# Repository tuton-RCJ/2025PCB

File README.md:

# 2025PCB
ツートンの基板・回路のリポジトリです。
ご自由にご覧下さい。

基板はすべてKiCAD7.0で設計し、JLCPCB様に発注しています。
1-TOKYOが東東京ノード大会で使用した基板です。
2-KANTOは関東ブロック大会で使用した基板です。
3-NAGOYAは名古屋全国大会で使用した基板です。

# 3-NAGOYA
全国大会機「シロ」の基板です。
全部で6枚です。
## 基板一覧
* 01 MAIN
    メイン基板。一層目に置きます。
* 02 LINE
    ラインセンサ基板。一層目に置きます。
    フォトリフレクタは16個使います。
* 03 FRONT
    正面基板。ToFセンサを搭載しています。
* 04 RESCUE
    二層目と一層目をつなぐ基板です。
* 05 PWR
    電源基板。メイン基板とスペーサで接続します。
* 06 UI
    UI基板。ディスプレイを搭載しています。使いませんでした。
* 07 OpenMV
    OpenMVに取り付けるシールドです。UARTをXHに引き出しました。

# 2-KANTO
関東機体「MIKE（ミケ）」の基板です。
今回は全部で3枚です。

## 基板一覧
* 01 MAIN
    メイン基板。一層目に置きます。
* 02 LINE
    ラインセンサ基板。一層目に置きます。
    フォトリフレクタは16個使います。
* 03 FRONT
    当初は作る予定だったが使わなくなりました。
    空っぽなのもつまらないので回路図に落書きしました。
* 04 PWR
    電源基板。二層目に置きます。

# 1-TOKYO
東東京機体「ポチ」の基板です。
全部で5枚（+α）です。

## 基板一覧
* 01 main
    メイン基板。
    * 完成 2024/10/01
    * 発注 2024/10/02
* 02 top
    ハンドルの上に置く基板。UI基板。
    * 設計中
    * 使わなかった
* 03 front
    正面の基板。カメラとToFを置く。
    * 完成 2024/10/01
    * 発注 2024/10/02
* 04 line
    ラインセンサ基板。
    * 完成 2024/06/25
    * 発注 2024/06/26
* 05 PWR
    電源基板。
    3.3V, 5V, 7.2Vを生成。
    * 完成 2024/06/25
    * 発注 2024/06/26
* 06 WRITER
    書き込み基板
    * 完成 2024/05/14
    * 発注 2024/05/16
* 07 frame
    フレームを基板で作ろうとしたが結局3Dプリンタで作った。
* 08 REG_mod
    TPS5430を使用した自作DCDC。
    電源基板に乗せる。
    * 完成 2024/06/25
    * 発注 2024/06/26
* 09 ToF_mod
    自作ToF（VL53L0X）
    * 完成　2024/08/17
## リポジトリ構成
* 01-main ~ 08-REG_mod 
    それぞれの基板のKiCADのプロジェクト。
* library
    KiCADで使用しているライブラリ。
    シンボル、フットプリント、3Dモデル。
* pin
    STM32のピン配置を考えるために使用したSTM32CubeIDEのファイル。
    かなり雑です。
* ver1、ver2
    過去作の保管場所。
    何らかの事情でボツになった設計たちです。
* PDFファイル
    完成した基板の回路図はPDFにしてあります。
    ブラウザ上で見ることができると思います。

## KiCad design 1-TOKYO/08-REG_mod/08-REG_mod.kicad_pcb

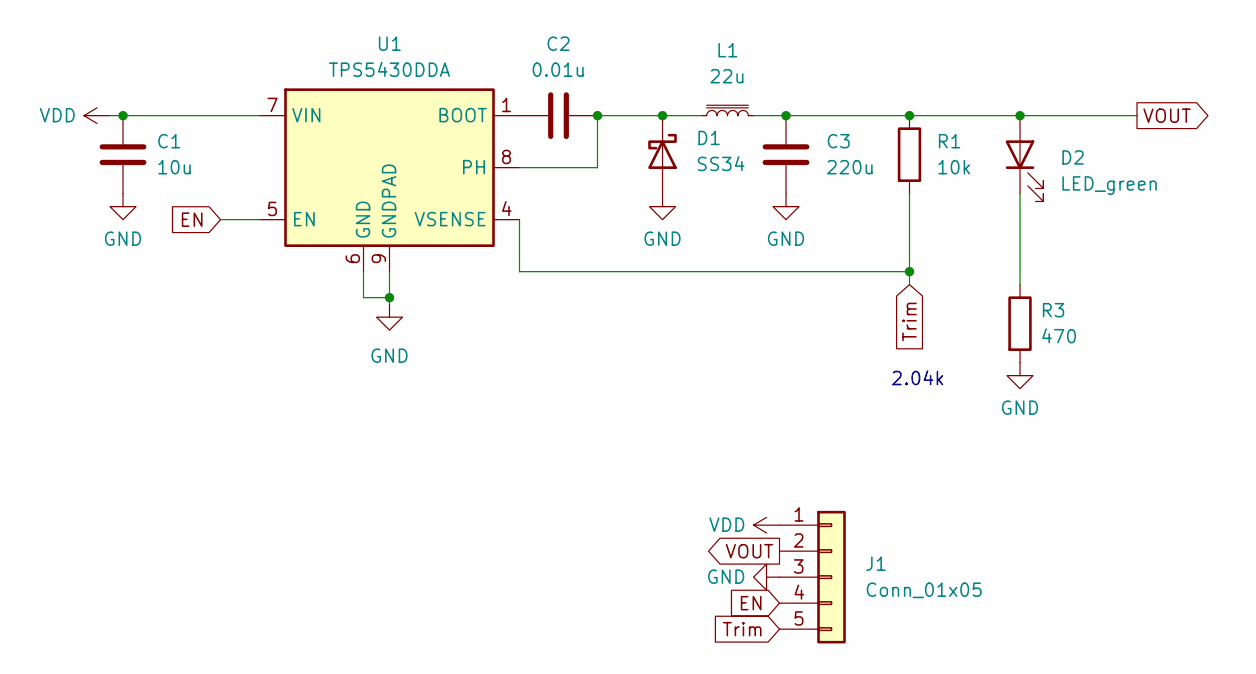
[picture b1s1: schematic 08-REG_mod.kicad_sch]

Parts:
C1: 10u; C_0805_2012Metric; LCSC C15850
C2: 0.01u; C_0603_1608Metric; LCSC C57112
C3: 220u; CP_Radial_D6.3mm_P2.50mm
D1: SS34; D_SMA; LCSC C8678
D2: LED_green; LED_0805_2012Metric; LCSC C2297
J1: Conn_01x05; PinHeader_1x05_P2.54mm_Horizontal
L1: 22u; FXL1040-220-M; LCSC C475917
R1: 10k; R_0603_1608Metric; LCSC C25804
R3: 470; R_0603_1608Metric; LCSC C23179
U1: TPS5430DDA; TI_SO-PowerPAD-8_ThermalVias

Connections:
EN: J1.4, U1.5 (EN)
GND: C1.2, C3.2, D1.2 (A), J1.3, U1.6 (GND), U1.9 (GNDPAD); also elsewhere on the board
unnamed: C2.2, D1.1 (K), L1.1, U1.8 (PH)
unnamed 3: D2.1 (K); also elsewhere on the board
unnamed: C2.1, U1.1 (BOOT)
Trim: J1.5, R1.2, U1.4 (VSENSE)
VDD: C1.1, J1.1, U1.7 (VIN)
VOUT: C3.1, D2.2 (A), J1.2, L1.2, R1.1

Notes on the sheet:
2.04k

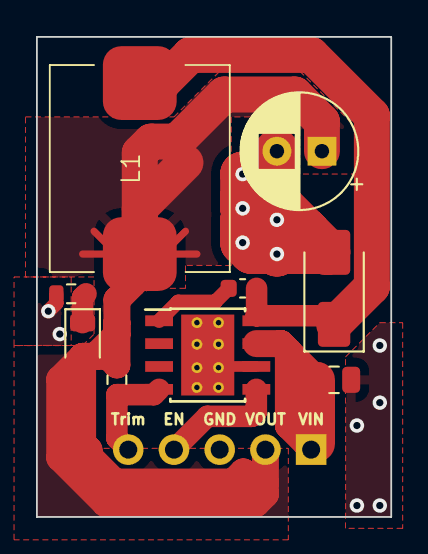
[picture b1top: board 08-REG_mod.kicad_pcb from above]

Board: 2 copper layers, 19.7 x 26.7 mm, 10 parts (1 on the bottom side), 8 nets.

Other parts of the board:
R2: 470; R_0603_1608Metric

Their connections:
GND: R2.2; also elsewhere on the board
unnamed 3: R2.1; also elsewhere on the board

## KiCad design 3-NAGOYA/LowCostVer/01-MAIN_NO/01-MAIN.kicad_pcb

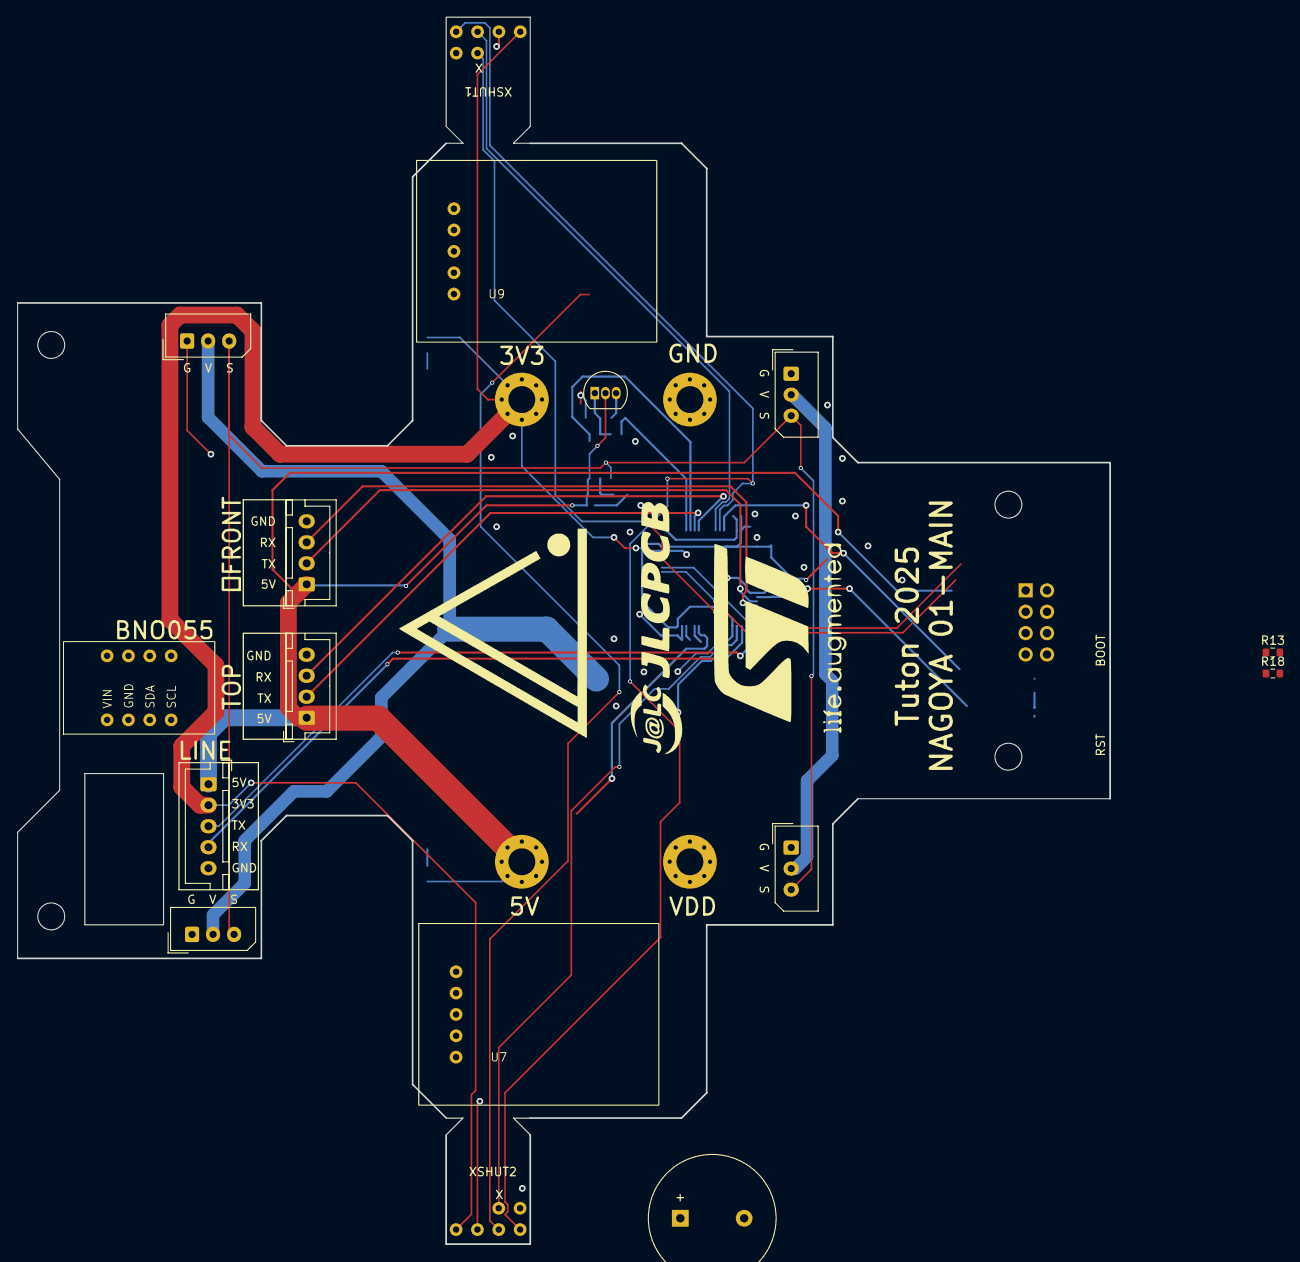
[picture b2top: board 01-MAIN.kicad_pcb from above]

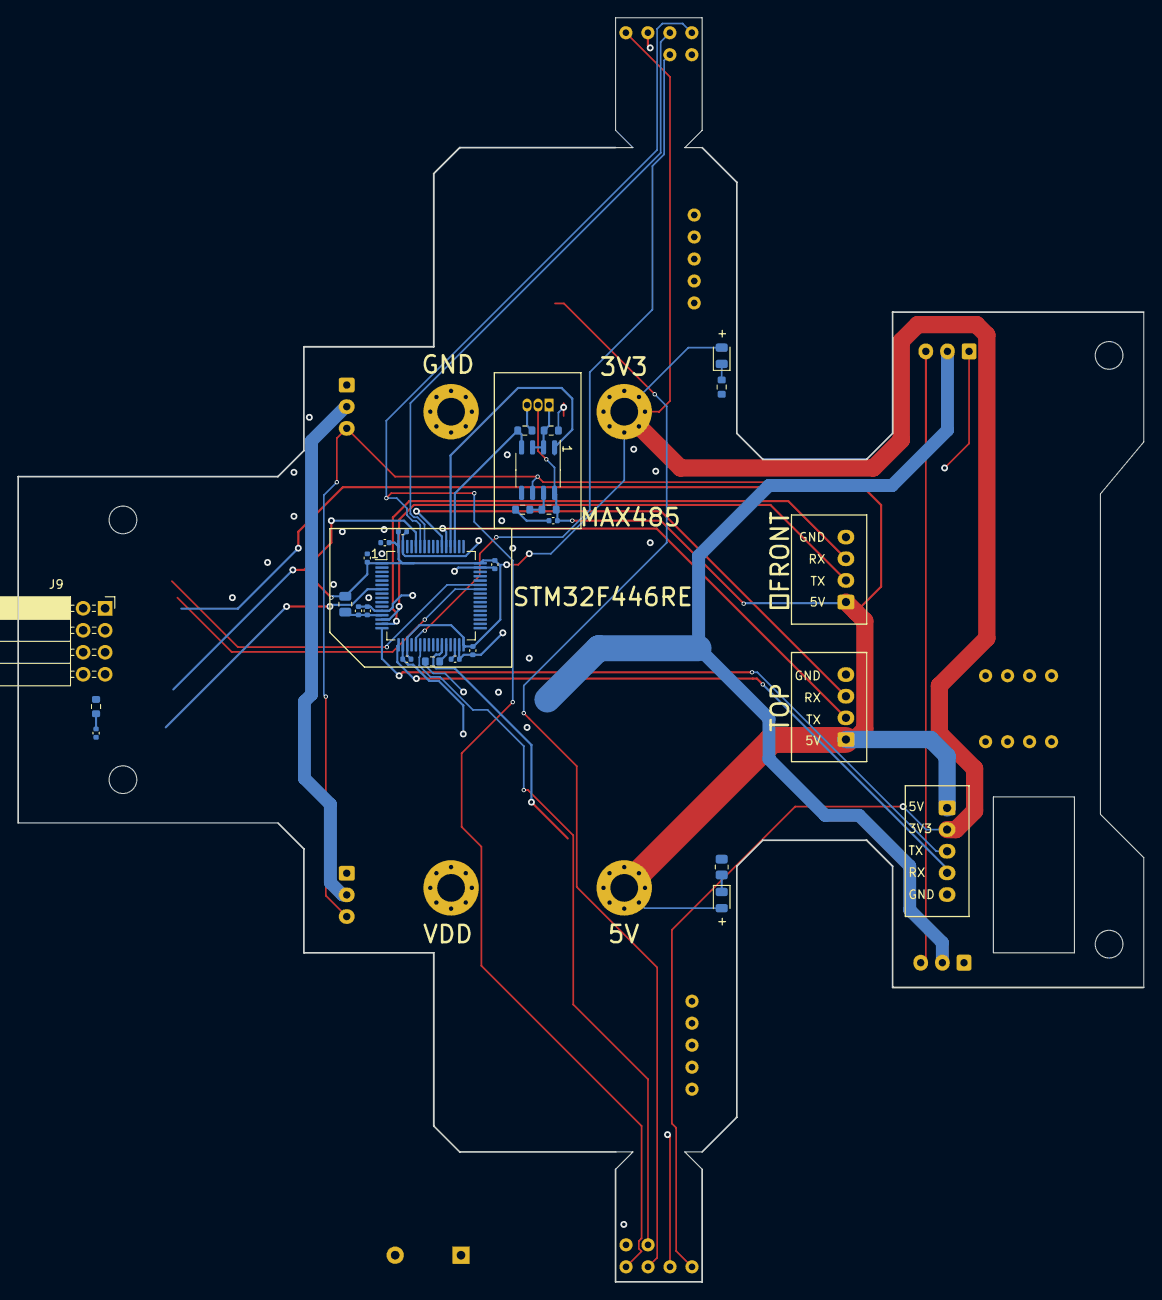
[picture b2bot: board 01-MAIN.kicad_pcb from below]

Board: 2 copper layers, 130.0 x 145.9 mm, 45 parts (25 on the bottom side), 34 nets.

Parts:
BZ1: Buzzer; Buzzer_15x7.5RM7.6
C1, C3, C4, C5, C6, C8, C9, C10: 100n; C_0402_1005Metric
C2, C7: 4.7u; C_0402_1005Metric
C11: 1u; C_0402_1005Metric
D1, D2: LED_GREEN; LED_0805_2012Metric
FB1: FerriteBead; R_0805_2012Metric
H1: ToMainVDD; MountingHole_3.2mm_M3_Pad_Via
H2: ToMainGND; MountingHole_3.2mm_M3_Pad_Via
H3: ToMain3V3; MountingHole_3.2mm_M3_Pad_Via
H4: ToMain5V; MountingHole_3.2mm_M3_Pad_Via
J1: Front; JST_XH_B4B-XH-A_1x04_P2.50mm_Vertical
J2: Top; JST_XH_B4B-XH-A_1x04_P2.50mm_Vertical
J3: toLINE; JST_XH_B5B-XH-A_1x05_P2.50mm_Vertical
J5, J6, J7, J8: STS3032; Molex_SPOX_5267-03A_1x03_P2.50mm_Vertical
J9: WRITER CONN; PinSocket_2x04_P2.54mm_Horizontal
Q1: 2SA1015; TO-92_Inline
R1: 7.5k; R_0603_1608Metric
R2, R6: 10k; R_0603_1608Metric
R3: 20k; R_0603_1608Metric
R4, R5, R13, R18: 2.2k; R_0603_1608Metric
R7: 470; R_0603_1608Metric
R8: 1k; R_0805_2012Metric
U1: STM32F446RETx; LQFP-64_10x10mm_P0.5mm
U2: MAX485ESA; SOP-8_3.9x4.9mm_P1.27mm
U3, U5: vl53l0x_vertical
U4: BNO055
U7, U9: TPS5430_horizontal

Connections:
+3V3: C3.2, C4.2, C5.2, C6.2, C7.1, C8.2, D1.2 (A), FB1.1, H3.1, J3.2, J9.1, U1.1 (VBAT), U1.19 (VDD), U1.32 (VDD), U1.48 (VDD), U1.64 (VDD), U3.1 (3V3), U4.1 (VIN), U5.1 (3V3)
+5V: C9.1, D2.2 (A), H4.1, J1.1, J2.1, J3.1, Q1.2 (C), R4.1, U2.8 (VCC)
BOOT0: J9.4, R2.1, U1.60 (BOOT0)
GND: BZ1.2 (+), C1.1, C2.2, C3.1, C4.1, C5.1, C6.1, C7.2, C8.1, C9.2, C10.1, C11.1, H2.1, J1.4, J2.4, J3.5, J5.1, J6.1, J7.1, J8.1, J9.3, R2.2, R3.2, R5.1, R6.2, R7.1, R8.1, R13.2, R18.2, U1.12 (VSSA), U1.18 (VSS), U1.31 (VSS), U1.47 (VSS), U1.63 (VSS), U2.5 (GND), U3.2 (GND), U4.2 (GND), U5.2 (GND), U7.3 (GND), U9.3 (GND)
I2C1_SCL: U1.58 (PB6), U3.3 (SCL), U4.4 (SCL), U5.3 (SCL)
I2C1_SDA: U1.59 (PB7), U3.4 (SDA), U4.3 (SDA), U5.4 (SDA)
NRST: C1.2, J9.6, U1.7 (NRST)
unnamed: D1.1 (K), R7.2
unnamed: D2.1 (K), R8.2
unnamed: J5.2, J6.2, U7.2 (VOUT)
unnamed: J7.2, J8.2, U9.2 (VOUT)
unnamed: Q1.3 (B), R1.1
unnamed: Q1.1 (E), R3.1, U2.2 (~RE), U2.3 (DE)
unnamed: R6.1, U1.28 (PB2)
unnamed: C2.1, U1.30 (VCAP_1)
unnamed: C10.2, C11.2, FB1.2, U1.13 (VDDA)
unnamed: R4.2, R5.2, U2.7 (B)
unnamed: R13.1, U7.5 (Trim)
unnamed: R18.1, U9.5 (Trim)
STS_SIG: J5.3, J6.3, J7.3, J8.3, U2.6 (A)
UART1_RX: J9.7, U1.43 (PA10)
UART1_TX: J9.5, U1.42 (PA9)
UART2_RX: J3.4, U1.17 (PA3)
UART2_TX: J3.3, U1.16 (PA2)
UART3_RX: U1.52 (PC11), U2.1 (RO)
UART3_TX: R1.2, U1.51 (PC10), U2.4 (DI)
UART4_RX: J1.3, U1.15 (PA1)
UART4_TX: J1.2, U1.14 (PA0)
UART5_RX: J2.3, U1.54 (PD2)
UART5_TX: J2.2, U1.53 (PC12)
VDD: H1.1, U7.1 (VIN), U9.1 (VIN)
XSHUT1: U1.21 (PA5), U3.5 (XSHUT)
XSHUT2: U1.22 (PA6), U5.5 (XSHUT)
buzzer: BZ1.1 (-), U1.27 (PB1)

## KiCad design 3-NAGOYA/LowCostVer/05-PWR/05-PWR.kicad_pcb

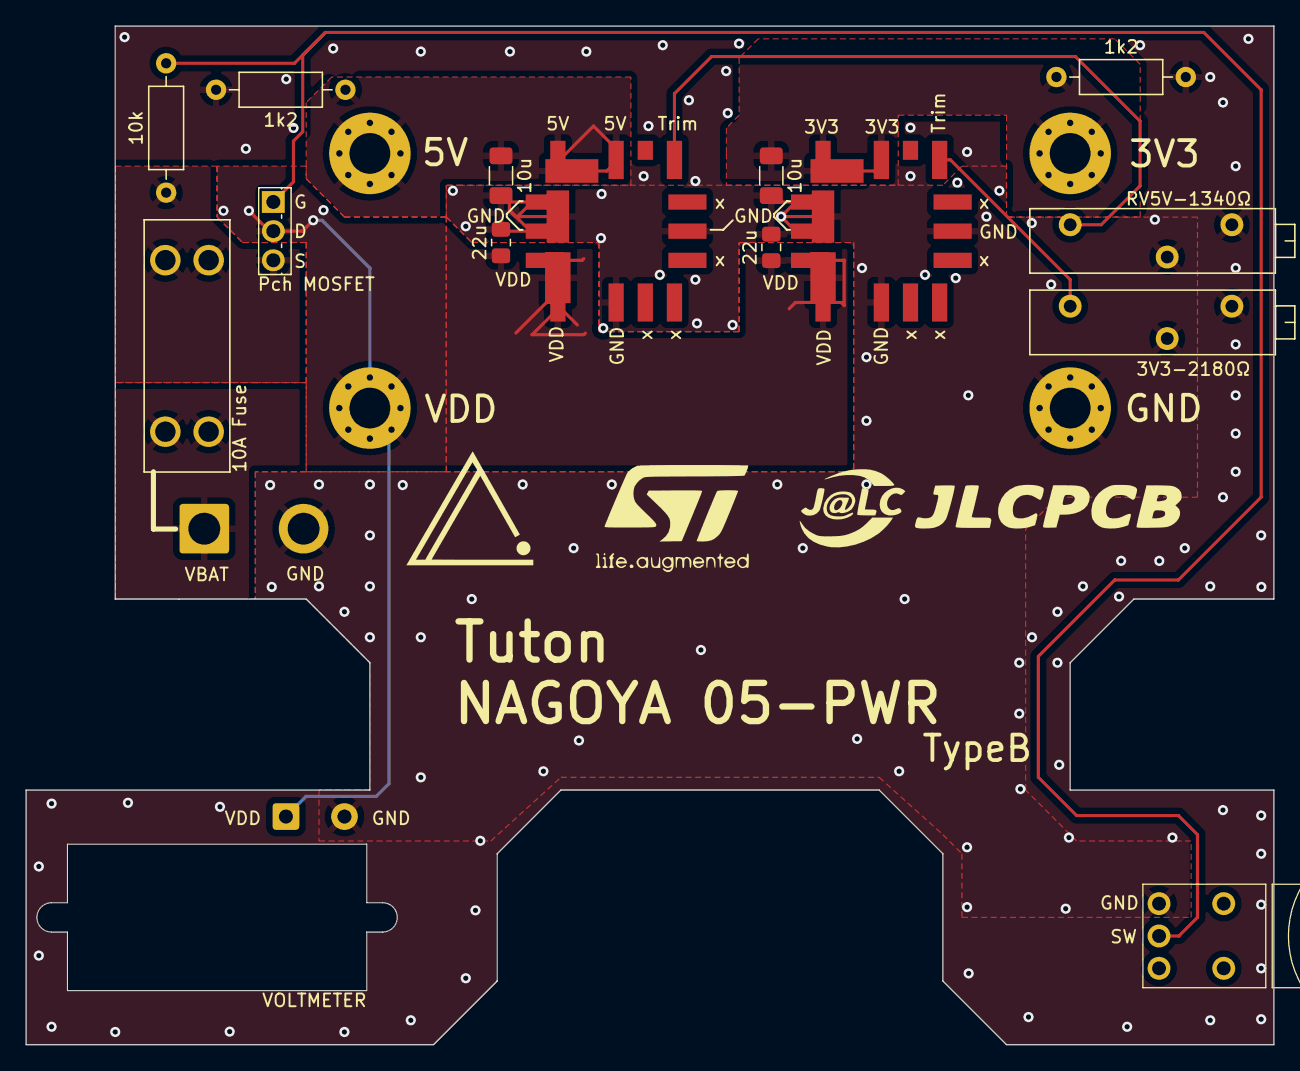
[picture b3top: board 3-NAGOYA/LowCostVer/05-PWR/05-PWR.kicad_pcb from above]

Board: 2 copper layers, 98.0 x 80.0 mm, 20 parts (0 on the bottom side), 9 nets.

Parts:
1k2, 1k2#2: 1.2k; R_Axial_DIN0207_L6.3mm_D2.5mm_P10.16mm_Horizontal
3V3-2180Ω: 3kΩ; Potentiometer_Bourns_3006P_Horizontal
10k: 10k; R_Axial_DIN0207_L6.3mm_D2.5mm_P10.16mm_Horizontal
10u, 10u#2: 10uF; C_1206_3216Metric_Pad1.33x1.80mm_HandSolder
22u, 22u#2: 22uF; C_0805_2012Metric_Pad1.18x1.45mm_HandSolder
F1: Fuse; FUSE_3557-15
H1: ToMainVDD; MountingHole_3.2mm_M3_Pad_Via
H2: ToMainGND; MountingHole_3.2mm_M3_Pad_Via
H3: ToMain3V3; MountingHole_3.2mm_M3_Pad_Via
H4: ToMain5V; MountingHole_3.2mm_M3_Pad_Via
J1: voltmeter; SolderWire-0.5sqmm_1x02_P4.6mm_D0.9mm_OD2.1mm
J2: Battery; SolderWire-2sqmm_1x02_P7.8mm_D2mm_OD3.9mm
Q1: Q_PMOS_GDS; TO-251-3_Vertical
RV5V-1340Ω: 3kΩ; Potentiometer_Bourns_3006P_Horizontal
SW1: SW_SPST; AkizukiSmallRockerSwitchHorizontal
U1, U2: OKL-T6-W12N-C-SMD

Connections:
+3V3: 1k2.1, 10u#2.1, H3.1, U1.4 (Vout), U1.5 (Sense)
+5V: 1k2#2.1, 10u.1, H4.1, U2.4 (Vout), U2.5 (Sense)
GND: 1k2.2, 1k2#2.2, 3V3-2180Ω.2, 3V3-2180Ω.3, 10u.2, 10u#2.2, 22u.2, 22u#2.2, H2.1, J1.2, J2.2, RV5V-1340Ω.2, RV5V-1340Ω.3, SW1.1 (A), U1.1 (ON/OFF), U1.3 (GND), U1.7 (GND), U2.1 (ON/OFF), U2.3 (GND), U2.7 (GND)
unnamed: F1.2, J2.1
unnamed: 10k.2, Q1.1 (G), SW1.2 (B)
unnamed: 10k.1, F1.1, Q1.3 (S)
unnamed: 3V3-2180Ω.1, U1.6 (Trim)
unnamed: RV5V-1340Ω.1, U2.6 (Trim)
VDD: 22u.1, 22u#2.1, H1.1, J1.1, Q1.2 (D), U1.2 (Vin), U2.2 (Vin)

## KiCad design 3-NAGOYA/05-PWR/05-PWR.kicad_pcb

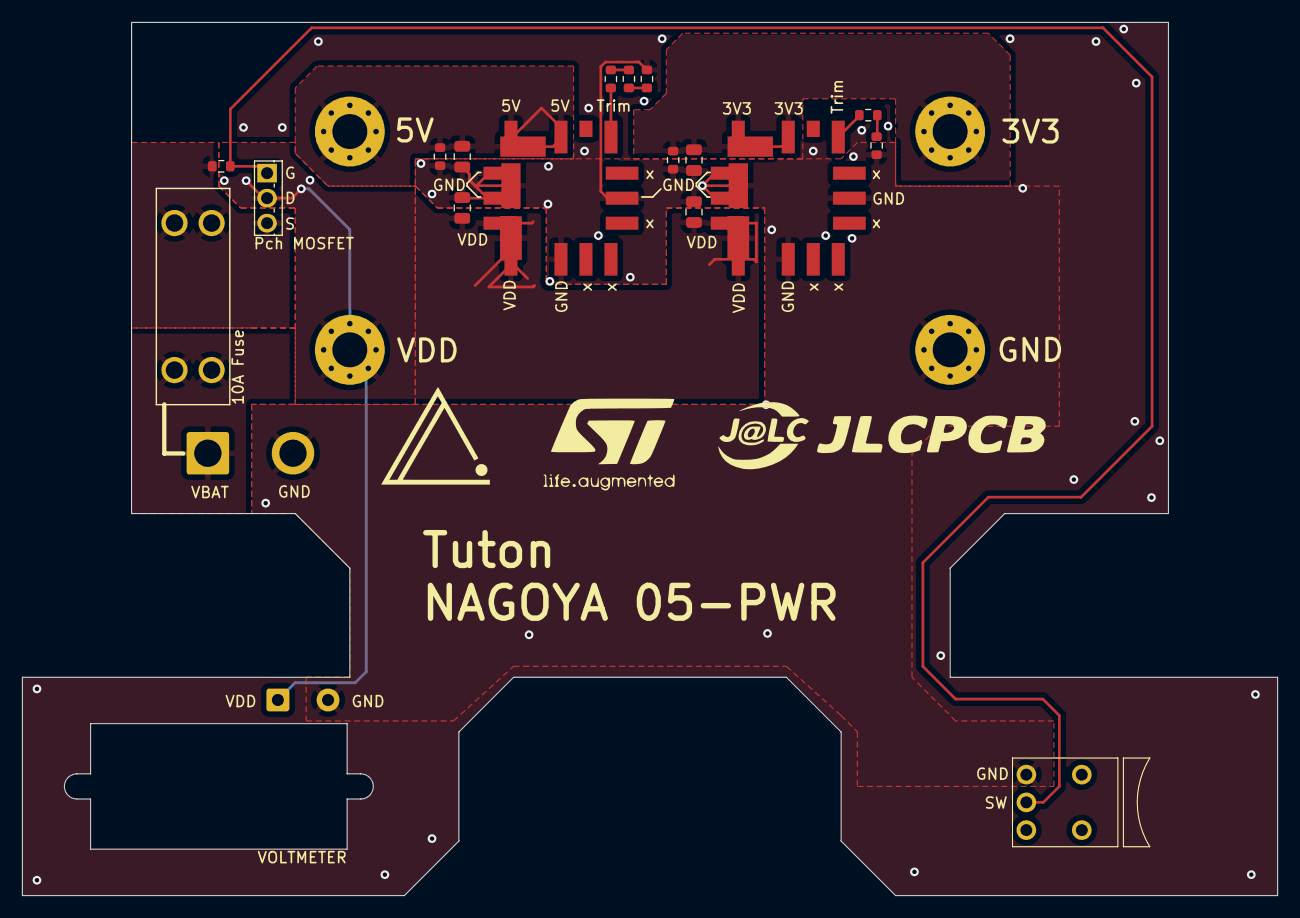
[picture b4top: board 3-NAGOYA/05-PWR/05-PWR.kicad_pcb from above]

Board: 2 copper layers, 115.0 x 80.0 mm, 23 parts (0 on the bottom side), 12 nets.

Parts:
C1, C2: 22uF; C_0805_2012Metric
C3, C4: 10uF; C_0805_2012Metric
F1: Fuse; FUSE_3557-15
H1: ToMainVDD; MountingHole_3.2mm_M3_Pad_Via
H2: ToMainGND; MountingHole_3.2mm_M3_Pad_Via
H3: ToMain3V3; MountingHole_3.2mm_M3_Pad_Via
H4: ToMain5V; MountingHole_3.2mm_M3_Pad_Via
J1: voltmeter; SolderWire-0.5sqmm_1x02_P4.6mm_D0.9mm_OD2.1mm
J2: Battery; SolderWire-2sqmm_1x02_P7.8mm_D2mm_OD3.9mm
Q1: Q_PMOS_GDS; TO-251-3_Vertical
R1: 1k; R_0603_1608Metric
R2: 330; R_0603_1608Metric
R3: 10; R_0603_1608Metric
R4: 1.5k; R_0603_1608Metric
R5: 680; R_0603_1608Metric
R6, R7: 1.2k; R_0603_1608Metric
R8: 10k; R_0603_1608Metric
SW1: SW_SPST; AkizukiSmallRockerSwitchHorizontal
U1, U2: OKL-T6-W12N-C-SMD

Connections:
+3V3: C3.1, H3.1, R6.1, U1.4 (Vout), U1.5 (Sense)
+5V: C4.1, H4.1, R7.1, U2.4 (Vout), U2.5 (Sense)
GND: C1.2, C2.2, C3.2, C4.2, H2.1, J1.2, J2.2, R3.2, R5.2, R6.2, R7.2, SW1.1 (A), U1.1 (ON/OFF), U1.3 (GND), U1.7 (GND), U2.1 (ON/OFF), U2.3 (GND), U2.7 (GND)
unnamed: F1.2, J2.1
unnamed: Q1.1 (G), R8.2, SW1.2 (B)
unnamed: F1.1, Q1.3 (S), R8.1
unnamed: R1.2, R2.1
unnamed: R2.2, R3.1
unnamed: R4.2, R5.1
unnamed: R4.1, U1.6 (Trim)
unnamed: R1.1, U2.6 (Trim)
VDD: C1.1, C2.1, H1.1, J1.1, Q1.2 (D), U1.2 (Vin), U2.2 (Vin)

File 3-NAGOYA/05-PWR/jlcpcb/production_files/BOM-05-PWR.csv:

Comment,Designator,Footprint,LCSC
10uF,"C3,C4",C_0805_2012Metric,C15850
1k,R1,R_0603_1608Metric,C21190
1.2k,"R6,R7",R_0603_1608Metric,C22765
1.5k,R4,R_0603_1608Metric,C22843
10,R3,R_0603_1608Metric,C22859
330,R2,R_0603_1608Metric,C23138
680,R5,R_0603_1608Metric,C23228
10k,R8,R_0603_1608Metric,C25804
22uF,"C1,C2",C_0805_2012Metric,C45783
Fuse,F1,FUSE_3557-15,
~,U2,OKL-T6-W12N-C-SMD,
Q_PMOS_GDS,Q1,TO-251-3_Vertical,
SW_SPST,SW1,AkizukiSmallRockerSwitchHorizontal,
~,U1,OKL-T6-W12N-C-SMD,

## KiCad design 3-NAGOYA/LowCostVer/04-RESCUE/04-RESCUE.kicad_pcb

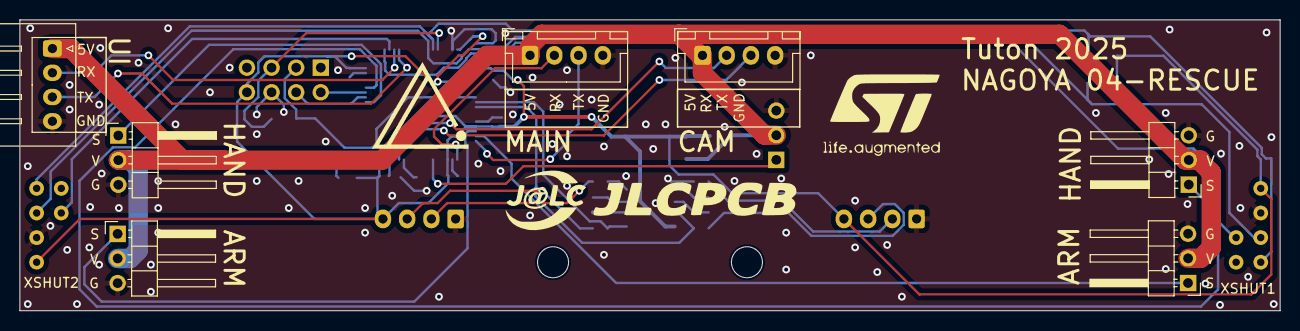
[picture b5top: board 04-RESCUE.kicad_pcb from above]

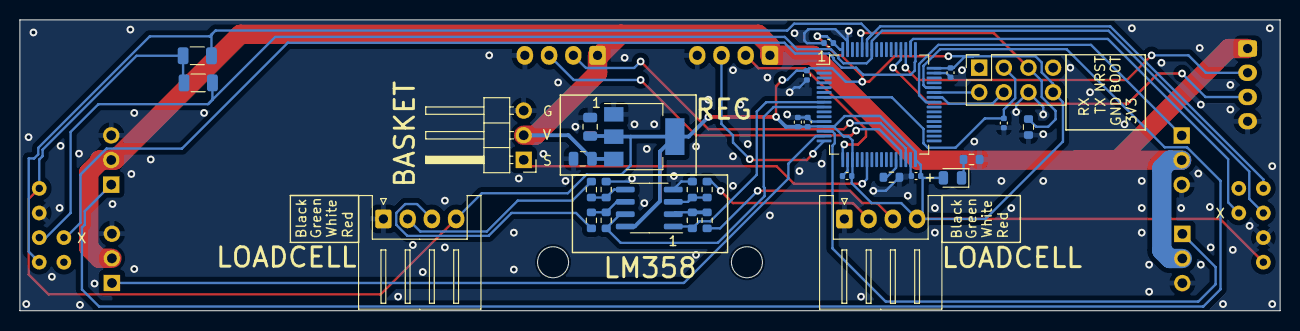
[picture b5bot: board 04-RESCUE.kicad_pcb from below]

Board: 2 copper layers, 130.0 x 30.0 mm, 40 parts (33 on the bottom side), 34 nets.

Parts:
C1, C2: 22u; C_0805_2012Metric
C8, C9, C10, C11, C12, C14, C15: 100n; C_0402_1005Metric
C13: 4.7u; C_0402_1005Metric
D1: LED_GREEN; LED_0805_2012Metric
J1: UI; JST_XH_S4B-XH-A_1x04_P2.50mm_Horizontal
J2: MAIN; JST_XH_B4B-XH-A_1x04_P2.50mm_Vertical
J3: LOADCELL_R; JST_XH_S4B-XH-A_1x04_P2.50mm_Horizontal
J4: WRITER CONN; PinSocket_2x04_P2.54mm_Vertical
J5: LOADCELL_L; JST_XH_S4B-XH-A_1x04_P2.50mm_Horizontal
J6: OpenMV; JST_XH_B4B-XH-A_1x04_P2.50mm_Vertical
M1: ServoBasketLeft; PinHeader_1x03_P2.54mm_Horizontal
M3: ServoArmLeft; PinHeader_1x03_P2.54mm_Horizontal
M4: ServoArmRight; PinHeader_1x03_P2.54mm_Horizontal
M5: ServoHandLeft; PinHeader_1x03_P2.54mm_Horizontal
M6: ServoHandRight; PinHeader_1x03_P2.54mm_Horizontal
R1, R2, R3, R6: 330; R_0603_1608Metric
R4, R5: 10k; R_0603_1608Metric
R7, R8, R9, R10: 1M; R_0603_1608Metric
R11: 470; R_0603_1608Metric
R12, R13: 10k; R_1206_3216Metric
U1: LM358; SOIC-8_3.9x4.9mm_P1.27mm
U2, U3: vl53l0x_vertical
U4: STM32F103RCTx; LQFP-64_10x10mm_P0.5mm
U5: AMS1117-3.3; SOT-223-3_TabPin2

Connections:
+3V3: C2.1, C8.2, C9.2, C10.2, C11.2, C12.2, C13.2, C14.2, D1.2 (A), J3.4, J4.8, J5.4, R12.1, R13.2, U1.8 (V+), U2.1 (3V3), U3.1 (3V3), U4.1 (VBAT), U4.13 (VDDA), U4.19 (VDD), U4.32 (VDD), U4.48 (VDD), U4.64 (VDD), U5.2 (VO)
+5V: C1.1, J1.1, J2.1, J6.1, M1.2 (+), M3.2 (+), M4.2 (+), M5.2 (+), M6.2 (+), U5.3 (VI)
BOOT0: J4.5, R4.1, U4.60 (BOOT0)
GND: C1.2, C2.2, C8.1, C9.1, C10.1, C11.1, C12.1, C13.1, C14.1, C15.1, J1.4, J2.4, J3.1, J4.6, J5.1, J6.4, M1.3 (-), M3.3 (-), M4.3 (-), M5.3 (-), M6.3 (-), R4.2, R5.1, R7.2, R9.2, R11.1, U1.4 (V-), U2.2 (GND), U3.2 (GND), U4.12 (VSSA), U4.18 (VSS), U4.31 (VSS), U4.47 (VSS), U4.63 (VSS), U5.1 (GND)
LOADCEL_L: R10.1, U1.1, U4.8 (PC0)
LOADCEL_R: R8.1, U1.7, U4.9 (PC1)
NRST: C15.2, J4.3, U4.7 (NRST)
unnamed: D1.1 (K), R11.2
unnamed: J3.2, R1.1
unnamed: J3.3, R2.2
unnamed: J5.2, R3.1
unnamed: J5.3, R6.2
unnamed: R3.2, R9.1, U1.3 (+)
unnamed: R6.1, R10.2, U1.2 (-)
unnamed: R1.2, R7.1, U1.5 (+)
unnamed: R2.1, R8.2, U1.6 (-)
unnamed: R5.2, U4.28 (PB2)
SCL: R13.1, U2.3 (SCL), U3.3 (SCL), U4.58 (PB6)
SDA: R12.2, U2.4 (SDA), U3.4 (SDA), U4.59 (PB7)
ServoArmLeft: M3.1 (PWM), U4.14 (PA0)
ServoArmRight: M4.1 (PWM), U4.15 (PA1)
ServoBasket: M1.1 (PWM), U4.22 (PA6)
ServoHandLeft: M5.1 (PWM), U4.41 (PA8)
ServoHandRight: M6.1 (PWM), U4.44 (PA11)
UART1_RX: J4.2, U4.43 (PA10)
UART1_TX: J4.4, U4.42 (PA9)
UART2_RX: J2.2, U4.17 (PA3)
UART2_TX: J2.3, U4.16 (PA2)
UART3_RX: J6.2, U4.30 (PB11)
UART3_TX: J6.3, U4.29 (PB10)
UART4_RX: J1.3, U4.52 (PC11)
UART4_TX: J1.2, U4.51 (PC10)
XSHUT1: U2.5 (XSHUT), U4.49 (PA14)
XSHUT2: U3.5 (XSHUT), U4.50 (PA15)

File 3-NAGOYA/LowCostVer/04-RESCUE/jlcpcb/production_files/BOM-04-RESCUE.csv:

Comment,Designator,Footprint,LCSC
100n,"C10,C11,C12,C14,C15,C8,C9",C_0402_1005Metric,C1525
10k,"R12,R13",R_1206_3216Metric,C17902
1M,"R10,R7,R8,R9",R_0603_1608Metric,C22935
LED_GREEN,D1,LED_0805_2012Metric,C2297
330,"R1,R2,R3,R6",R_0603_1608Metric,C23138
470,R11,R_0603_1608Metric,C23179
4.7u,C13,C_0402_1005Metric,C23733
10k,"R4,R5",R_0603_1608Metric,C25804
22u,"C1,C2",C_0805_2012Metric,C45783
LM358,U1,SOIC-8_3.9x4.9mm_P1.27mm,C5423
AMS1117-3.3,U5,SOT-223-3_TabPin2,C6186
STM32F103RCTx,U4,LQFP-64_10x10mm_P0.5mm,C8323
ServoArmRight,M4,PinHeader_1x03_P2.54mm_Horizontal,
MAIN,J2,JST_XH_B4B-XH-A_1x04_P2.50mm_Vertical,
OpenMV,J6,JST_XH_B4B-XH-A_1x04_P2.50mm_Vertical,
ServoHandLeft,M5,PinHeader_1x03_P2.54mm_Horizontal,
ServoArmLeft,M3,PinHeader_1x03_P2.54mm_Horizontal,
UI,J1,JST_XH_S4B-XH-A_1x04_P2.50mm_Horizontal,
ServoHandRight,M6,PinHeader_1x03_P2.54mm_Horizontal,
LOADCELL_L,J5,JST_XH_S4B-XH-A_1x04_P2.50mm_Horizontal,
~,U2,vl53l0x_vertical,
LOADCELL_R,J3,JST_XH_S4B-XH-A_1x04_P2.50mm_Horizontal,
ServoBasketLeft,M1,PinHeader_1x03_P2.54mm_Horizontal,
~,U3,vl53l0x_vertical,
WRITER CONN,J4,PinSocket_2x04_P2.54mm_Vertical,

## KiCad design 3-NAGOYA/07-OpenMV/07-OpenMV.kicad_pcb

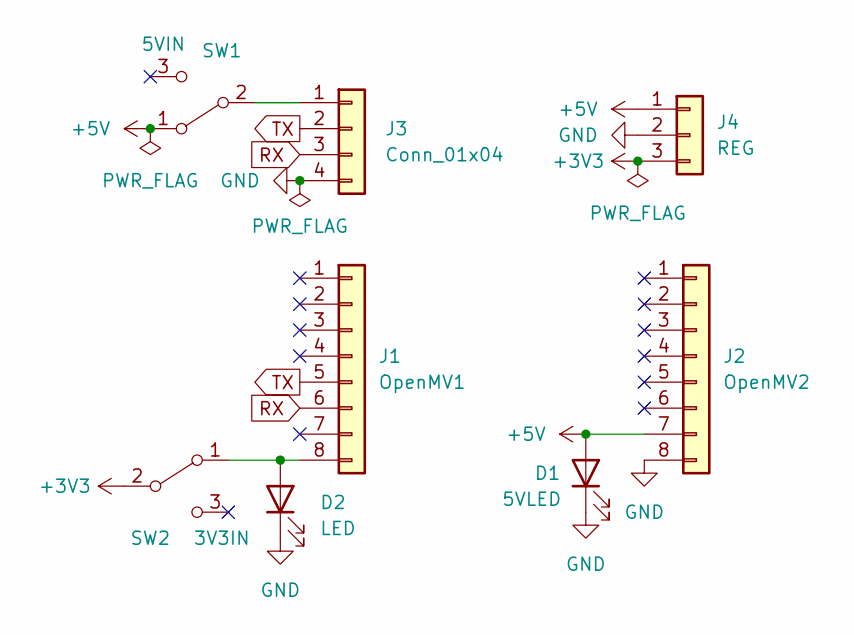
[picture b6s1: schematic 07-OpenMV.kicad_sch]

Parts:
D1: 5VLED; LED_D3.0mm_Clear
D2: LED; LED_D3.0mm_Clear
J1: OpenMV1; PinSocket_1x08_P2.54mm_Vertical
J2: OpenMV2; PinSocket_1x08_P2.54mm_Vertical
J3: Conn_01x04; JST_XH_S4B-XH-A_1x04_P2.50mm_Horizontal
J4: REG; PinHeader_1x03_P2.54mm_Vertical
SW1: 5VIN; SK-12D11VG3
SW2: 3V3IN; SK-12D11VG3

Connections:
+3V3: J4.3, SW2.2 (B)
+5V: D1.2 (A), J2.7, J4.1, SW1.1 (A)
GND: D1.1 (K), D2.1 (K), J2.8, J3.4, J4.2
unnamed: D2.2 (A), J1.8, SW2.1 (A)
unnamed: J3.1, SW1.2 (B)
RX: J1.6, J3.3
TX: J1.5, J3.2

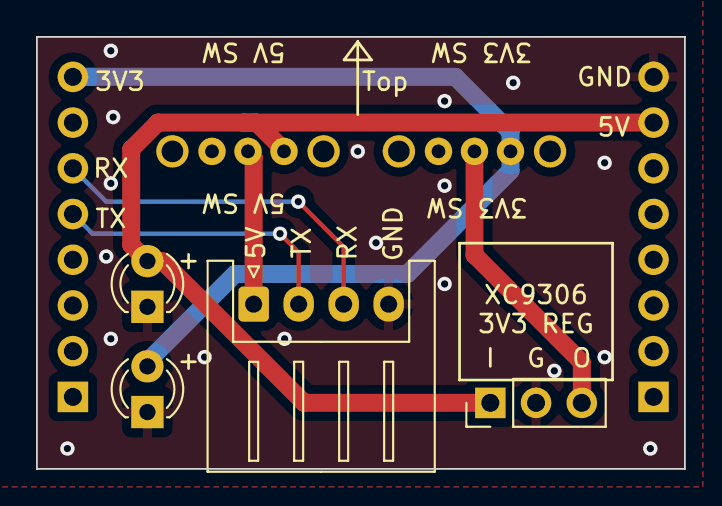
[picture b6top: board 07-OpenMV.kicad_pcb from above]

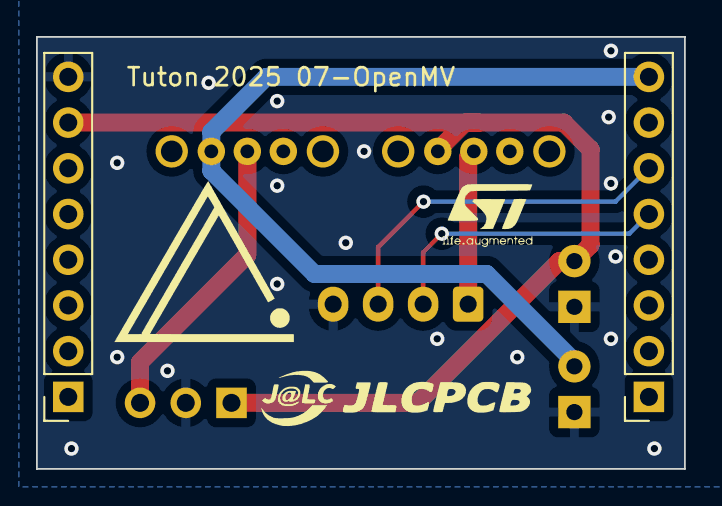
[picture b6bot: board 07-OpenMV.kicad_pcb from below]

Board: 2 copper layers, 36.0 x 24.0 mm, 8 parts (2 on the bottom side), 7 nets.

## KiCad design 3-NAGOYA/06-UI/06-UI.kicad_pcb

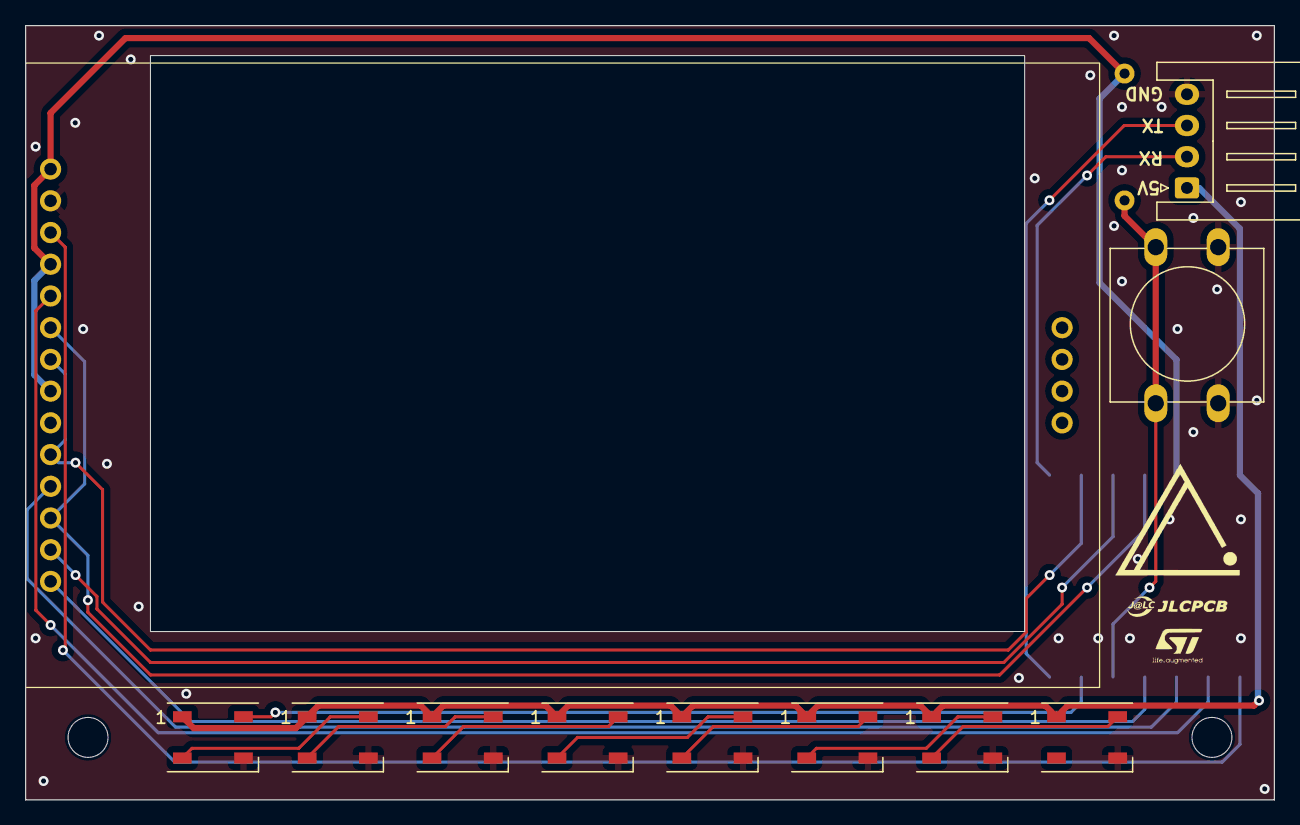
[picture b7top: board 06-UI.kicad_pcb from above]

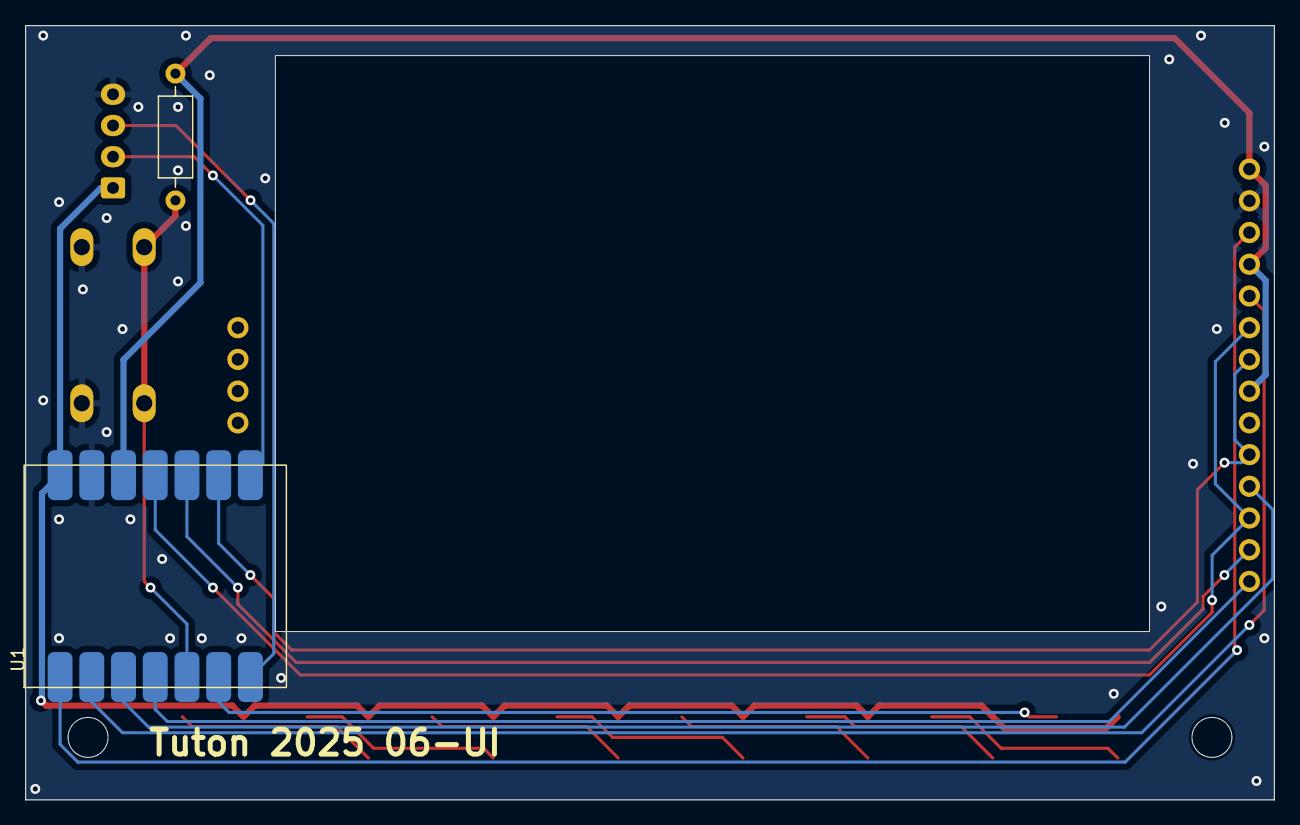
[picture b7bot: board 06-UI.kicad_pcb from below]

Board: 2 copper layers, 100.0 x 62.0 mm, 15 parts (2 on the bottom side), 21 nets.

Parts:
D1, D2, D3, D4, D5, D6, D7, D8: WS2812B; LED_WS2812B_PLCC4_5.0x5.0mm_P3.2mm
H1, H2: MountingHole; MountingHole_3.2mm_M3
J1: OpenMV Conn; JST_XH_S4B-XH-A_1x04_P2.50mm_Horizontal
R1: R; R_Axial_DIN0207_L6.3mm_D2.5mm_P10.16mm_Horizontal
SW1: SW_Push; SW_PUSH-12mm
U1: MOUDLE14P-SMD-2.54-21X17.8MM
U2: MS2807

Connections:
+3V3: R1.2, U1.12 (3V3), U2.1 (VCC), U2.4 (RESET), U2.8 (LED)
+5V: D1.1 (VDD), D2.1 (VDD), D3.1 (VDD), D4.1 (VDD), D5.1 (VDD), D6.1 (VDD), D7.1 (VDD), D8.1 (VDD), J1.1, U1.14 (5V)
Display_CS: U1.1 (D0/A0), U2.3 (CS)
Display_DC: U1.2 (D1/A1), U2.5 (DC/RS)
GND: D1.3 (VSS), D2.3 (VSS), D3.3 (VSS), D4.3 (VSS), D5.3 (VSS), D6.3 (VSS), D7.3 (VSS), D8.3 (VSS), J1.4, SW1.2, U1.13 (GND), U2.2 (GND)
MISO: U1.10 (D9), U2.13 (T_DOUT)
MOSI: U1.11 (D10), U2.6 (MOSI), U2.12 (T_DIN)
unnamed: D1.2 (DOUT), D2.4 (DIN)
unnamed: D2.2 (DOUT), D3.4 (DIN)
unnamed: D3.2 (DOUT), D4.4 (DIN)
unnamed: D4.2 (DOUT), D5.4 (DIN)
unnamed: D5.2 (DOUT), D6.4 (DIN)
unnamed: D6.2 (DOUT), D7.4 (DIN)
unnamed: D7.2 (DOUT), D8.4 (DIN)
RX: J1.2, U1.8 (RX/D7)
SCK: U1.9 (D8), U2.7 (SCK), U2.10 (T_CLK)
SW: R1.1, SW1.1, U1.5 (D4/SDA)
TX: J1.3, U1.7 (D6/TX)
Touch_CS: U1.3 (D2/A2), U2.11 (T_CS)
Touch_IRQ: U1.4 (D3/A3), U2.14 (T_IRQ)
WS2812B: D1.4 (DIN), U1.6 (D5/SCL)

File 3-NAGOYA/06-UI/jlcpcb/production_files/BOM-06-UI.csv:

Comment,Designator,Footprint,LCSC
OpenMV Conn,J1,JST_XH_S4B-XH-A_1x04_P2.50mm_Horizontal,
~,U1,MOUDLE14P-SMD-2.54-21X17.8MM,
~,U2,MS2807,
SW_Push,SW1,SW_PUSH-12mm,
R,R1,R_Axial_DIN0207_L6.3mm_D2.5mm_P10.16mm_Horizontal,
MountingHole,H2,MountingHole_3.2mm_M3,
MountingHole,H1,MountingHole_3.2mm_M3,
WS2812B,D8,LED_WS2812B_PLCC4_5.0x5.0mm_P3.2mm,
WS2812B,D7,LED_WS2812B_PLCC4_5.0x5.0mm_P3.2mm,
WS2812B,D6,LED_WS2812B_PLCC4_5.0x5.0mm_P3.2mm,
WS2812B,D5,LED_WS2812B_PLCC4_5.0x5.0mm_P3.2mm,
WS2812B,D4,LED_WS2812B_PLCC4_5.0x5.0mm_P3.2mm,
WS2812B,D3,LED_WS2812B_PLCC4_5.0x5.0mm_P3.2mm,
WS2812B,D2,LED_WS2812B_PLCC4_5.0x5.0mm_P3.2mm,
WS2812B,D1,LED_WS2812B_PLCC4_5.0x5.0mm_P3.2mm,

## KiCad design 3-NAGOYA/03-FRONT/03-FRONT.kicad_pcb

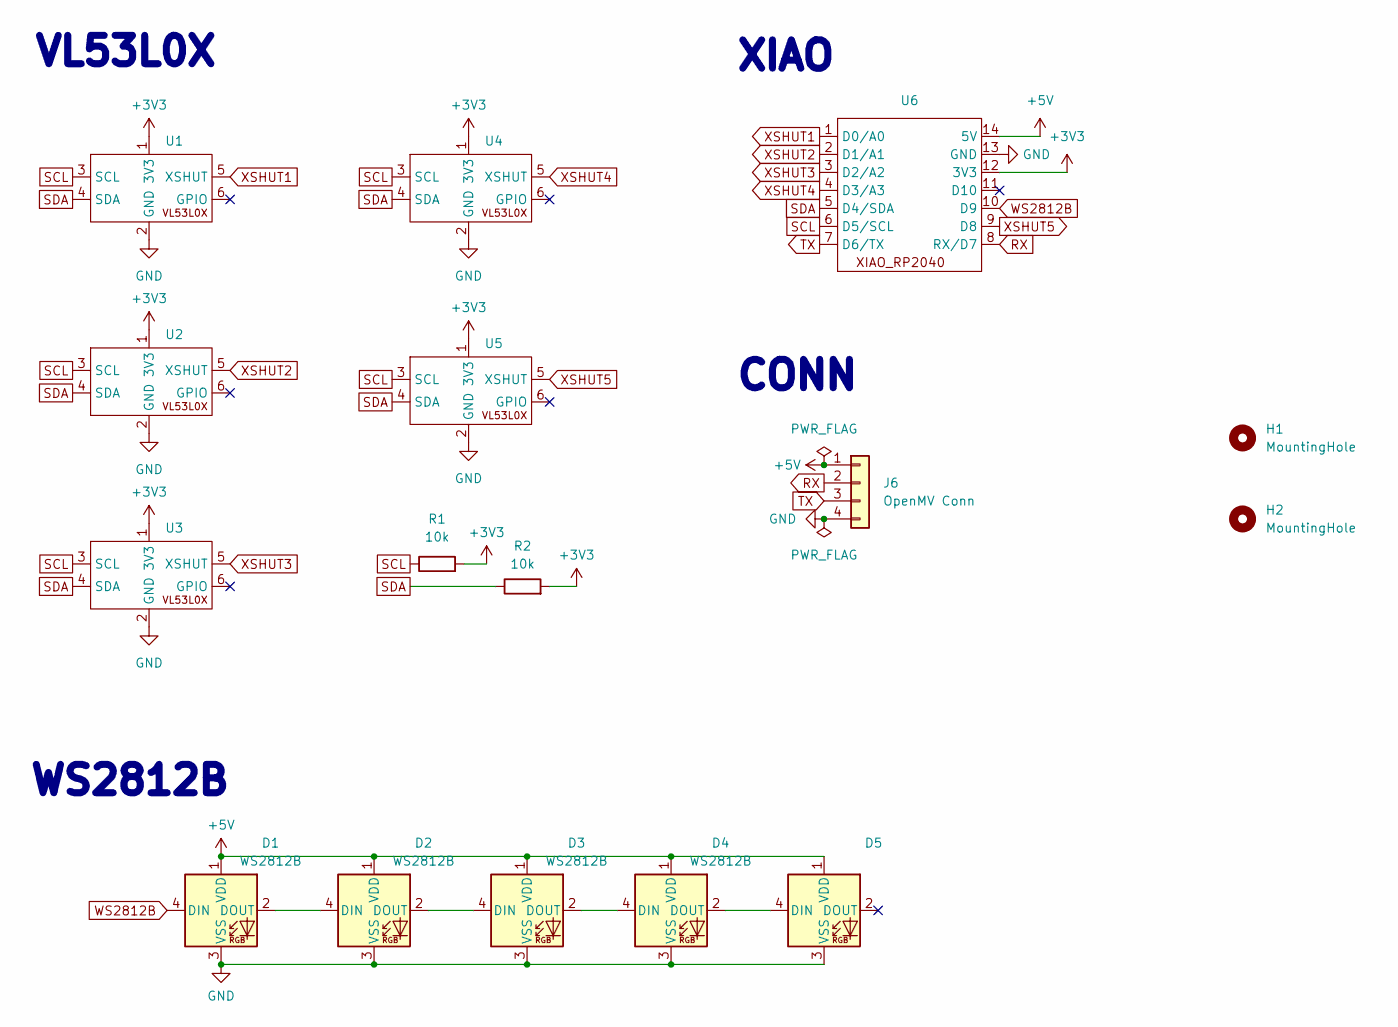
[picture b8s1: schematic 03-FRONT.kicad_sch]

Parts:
D1, D2, D3, D4, D5: WS2812B; LED_WS2812B_PLCC4_5.0x5.0mm_P3.2mm
H1, H2: MountingHole; MountingHole_3.2mm_M3
J6: OpenMV Conn; JST_XH_B4B-XH-A_1x04_P2.50mm_Vertical
R1, R2: 10k; R_Axial_DIN0207_L6.3mm_D2.5mm_P10.16mm_Horizontal
U1, U2, U3, U4, U5: VL53L0X_horizontal
U6: MOUDLE14P-2.54-21X17.8MM

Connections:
+3V3: R1.2, R2.2, U1.1 (3V3), U2.1 (3V3), U3.1 (3V3), U4.1 (3V3), U5.1 (3V3), U6.12 (3V3)
+5V: D1.1 (VDD), D2.1 (VDD), D3.1 (VDD), D4.1 (VDD), D5.1 (VDD), U6.14 (5V); also elsewhere on the board
GND: D1.3 (VSS), D2.3 (VSS), D3.3 (VSS), D4.3 (VSS), D5.3 (VSS), U1.2 (GND), U2.2 (GND), U3.2 (GND), U4.2 (GND), U5.2 (GND), U6.13 (GND); also elsewhere on the board
unnamed: D1.2 (DOUT), D2.4 (DIN)
unnamed: D2.2 (DOUT), D3.4 (DIN)
unnamed: D3.2 (DOUT), D4.4 (DIN)
unnamed: D4.2 (DOUT), D5.4 (DIN)
RX: U6.8 (RX/D7); also elsewhere on the board
SCL: R1.1, U1.3 (SCL), U2.3 (SCL), U3.3 (SCL), U4.3 (SCL), U5.3 (SCL), U6.6 (D5/SCL)
SDA: R2.1, U1.4 (SDA), U2.4 (SDA), U3.4 (SDA), U4.4 (SDA), U5.4 (SDA), U6.5 (D4/SDA)
TX: U6.7 (D6/TX); also elsewhere on the board
WS2812B: D1.4 (DIN), U6.10 (D9)
XSHUT1: U1.5 (XSHUT), U6.1 (D0/A0)
XSHUT2: U2.5 (XSHUT), U6.2 (D1/A1)
XSHUT3: U3.5 (XSHUT), U6.3 (D2/A2)
XSHUT4: U4.5 (XSHUT), U6.4 (D3/A3)
XSHUT5: U5.5 (XSHUT), U6.9 (D8)

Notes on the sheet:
XIAO
CONN
WS2812B
VL53L0X
